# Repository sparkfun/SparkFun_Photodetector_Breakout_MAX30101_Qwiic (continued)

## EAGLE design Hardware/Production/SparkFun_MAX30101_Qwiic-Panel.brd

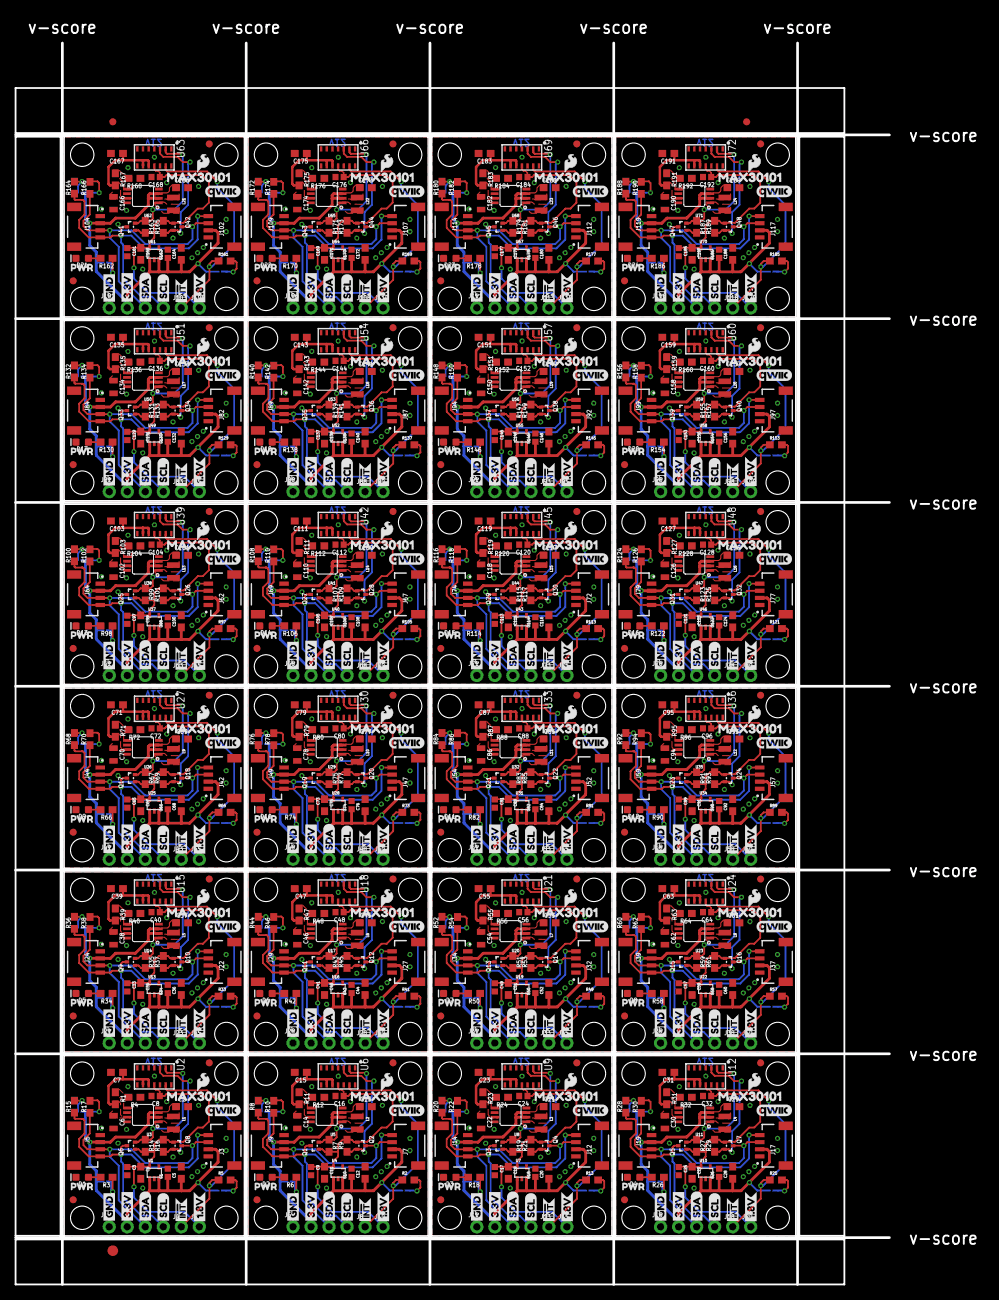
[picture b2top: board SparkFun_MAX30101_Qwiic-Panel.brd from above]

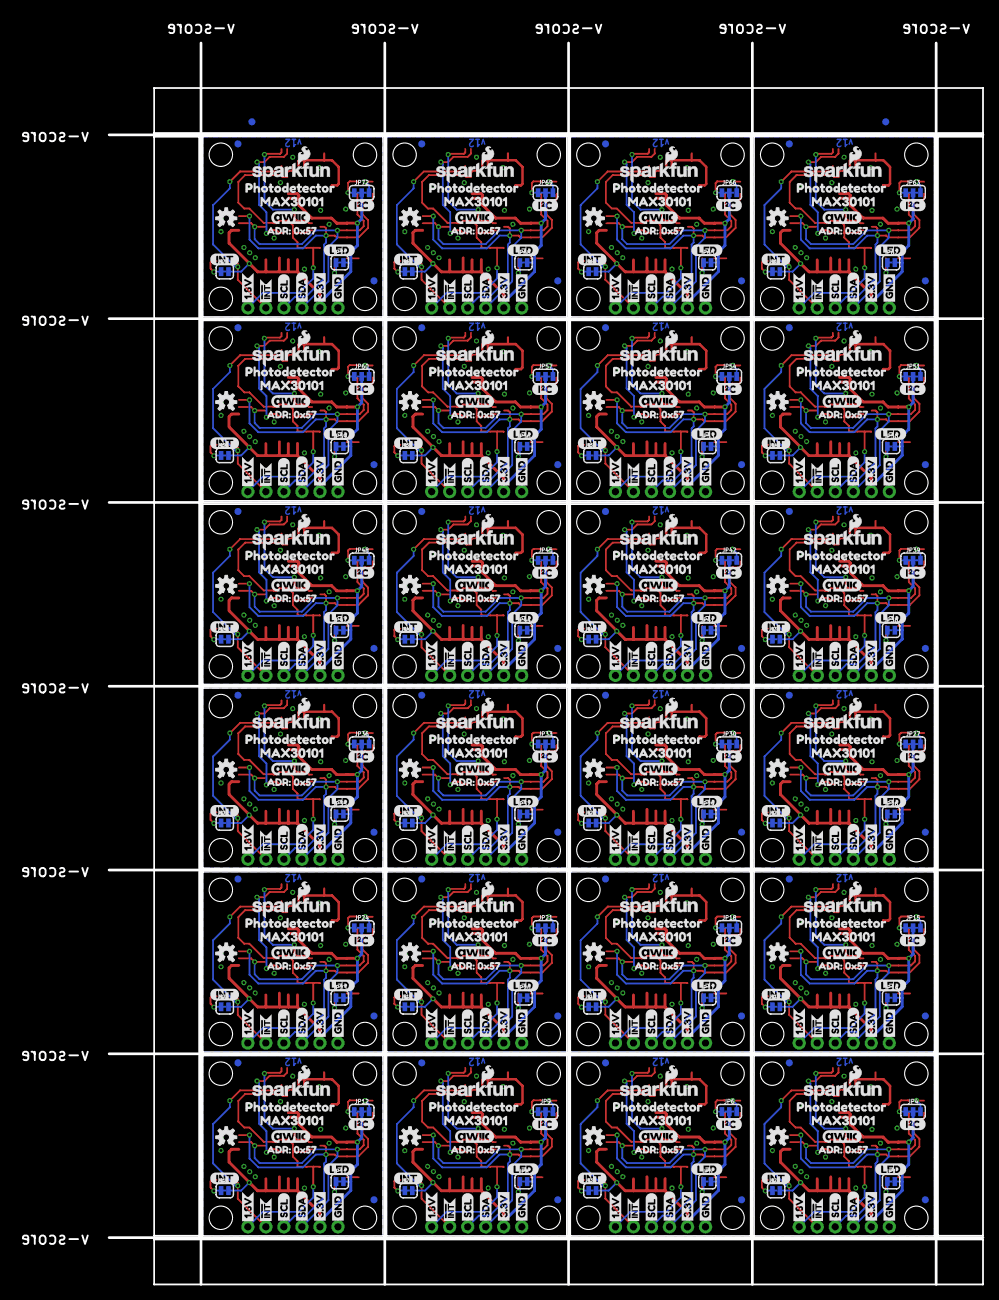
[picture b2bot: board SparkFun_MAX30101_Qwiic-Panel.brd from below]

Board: 2 copper layers, 123.2 x 175.0 mm, 1541 parts (482 on the bottom side), 384 nets.

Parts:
C1, C3, C8, C9, C10, C16, C17, C18, C24, C25, C26, C32, C33, C34, C40, C41, C42, C48, C49, C50, C56, C57, C58, C64, C65, C66, C72, C73, C74, C80, C81, C82, C88, C89, C90, C96, C97, C98, C104, C105, C106, C112, C113, C114, C120, C121, C122, C128, C129, C130, C136, C137, C138, C144, C145, C146, C152, C153, C154, C160, C161, C162, C168, C169, C170, C176, C177, C178, C184, C185, C186, C192: 0.1uF; 0402
C2, C4, C5, C7, C11, C12, C13, C15, C19, C20, C21, C23, C27, C28, C29, C31, C35, C36, C37, C39, C43, C44, C45, C47, C51, C52, C53, C55, C59, C60, C61, C63, C67, C68, C69, C71, C75, C76, C77, C79, C83, C84, C85, C87, C91, C92, C93, C95, C99, C100, C101, C103, C107, C108, C109, C111, C115, C116, C117, C119, C123, C124, C125, C127, C131, C132, C133, C135, C139, C140, C141, C143, C147, C148, C149, C151, C155, C156, C157, C159, C163, C164, C165, C167, C171, C172, C173, C175, C179, C180, C181, C183, C187, C188, C189, C191: 10uF; 0603
C6, C14, C22, C30, C38, C46, C54, C62, C70, C78, C86, C94, C102, C110, C118, C126, C134, C142, C150, C158, C166, C174, C182, C190: 22uF; 0805
D1, D2, D3, D4, D5, D6, D7, D8, D9, D10, D11, D12, D13, D14, D15, D16, D17, D18, D19, D20, D21, D22, D23, D24: RED; LED-0603
E$1, E$2, E$3, E$4: FIDUCIAL-1X2
E$5: FIDUCIAL-1.5X3
FID1, FID2, FID3, FID4, FID5, FID6, FID7, FID8, FID9, FID10, FID11, FID12, FID13, FID14, FID15, FID16, FID17, FID18, FID19, FID20, FID21, FID22, FID23, FID24, FID25, FID26, FID27, FID28, FID29, FID30, FID31, FID32, FID33, FID34, FID35, FID36, FID37, FID38, FID39, FID40, FID41, FID42, FID43, FID44, FID45, FID46, FID47, FID48, FID49, FID50, FID51, FID52, FID53, FID54, FID55, FID56, FID57, FID58, FID59, FID60, FID61, FID62, FID63, FID64, FID65, FID66, FID67, FID68, FID69, FID70, FID71, FID72, FID73, FID74, FID75, FID76, FID77, FID78, FID79, FID80, FID81, FID82, FID83, FID84, FID85, FID86, FID87, FID88, FID89, FID90, FID91, FID92, FID93, FID94, FID95, FID96: FIDUCIAL1X2; FIDUCIAL-1X2
J1, J6, J11, J16, J21, J26, J31, J36, J41, J46, J51, J56, J61, J66, J71, J76, J81, J86, J91, J96, J101, J106, J111, J116: PTH; 1X04_NO_SILK
J2, J4, J8, J10, J13, J15, J18, J20, J23, J25, J28, J30, J33, J35, J38, J40, J43, J45, J48, J50, J53, J55, J58, J60, J63, J65, J68, J70, J73, J75, J78, J80, J83, J85, J88, J90, J93, J95, J98, J100, J103, J105, J108, J110, J113, J115, J118, J120: 1X01_NO_SILK
J3, J5, J7, J9, J12, J14, J17, J19, J22, J24, J27, J29, J32, J34, J37, J39, J42, J44, J47, J49, J52, J54, J57, J59, J62, J64, J67, J69, J72, J74, J77, J79, J82, J84, J87, J89, J92, J94, J97, J99, J102, J104, J107, J109, J112, J114, J117, J119: QWIIC_RA; JST04_1MM_RA
JP1, JP5, JP8, JP11, JP14, JP17, JP20, JP23, JP26, JP29, JP32, JP35, JP38, JP41, JP44, JP47, JP50, JP53, JP56, JP59, JP62, JP65, JP68, JP71: LED; SMT-JUMPER_2_NC_TRACE_SILK
JP2, JP3, JP7, JP10, JP13, JP16, JP19, JP22, JP25, JP28, JP31, JP34, JP37, JP40, JP43, JP46, JP49, JP52, JP55, JP58, JP61, JP64, JP67, JP70: INT; SMT-JUMPER_2_NC_TRACE_SILK
JP4, JP6, JP9, JP12, JP15, JP18, JP21, JP24, JP27, JP30, JP33, JP36, JP39, JP42, JP45, JP48, JP51, JP54, JP57, JP60, JP63, JP66, JP69, JP72: I2C PU; SMT-JUMPER_3_2-NC_TRACE_SILK
L1, L2, L3, L4, L5, L6, L7, L8, L9, L10, L11, L12, L13, L14, L15, L16, L17, L18, L19, L20, L21, L22, L23, L24: 2.2μH; 0806
LOGO1, LOGO5, LOGO9, LOGO13, LOGO17, LOGO21, LOGO25, LOGO29, LOGO33, LOGO37, LOGO41, LOGO45, LOGO49, LOGO53, LOGO57, LOGO61, LOGO65, LOGO69, LOGO73, LOGO77, LOGO81, LOGO85, LOGO89, LOGO93: SFE_LOGO_NAME_FLAME.1_INCH; SFE_LOGO_NAME_FLAME_.1
LOGO2, LOGO6, LOGO10, LOGO14, LOGO18, LOGO22, LOGO26, LOGO30, LOGO34, LOGO38, LOGO42, LOGO46, LOGO50, LOGO54, LOGO58, LOGO62, LOGO66, LOGO70, LOGO74, LOGO78, LOGO82, LOGO86, LOGO90, LOGO94: OSHW-LOGOS; OSHW-LOGO-S
LOGO3, LOGO8, LOGO12, LOGO16, LOGO20, LOGO24, LOGO28, LOGO32, LOGO36, LOGO40, LOGO44, LOGO48, LOGO52, LOGO56, LOGO60, LOGO64, LOGO68, LOGO72, LOGO76, LOGO80, LOGO84, LOGO88, LOGO92, LOGO96: QWIIC_LOGO_5MM; QWIIC_5MM
LOGO4, LOGO7, LOGO11, LOGO15, LOGO19, LOGO23, LOGO27, LOGO31, LOGO35, LOGO39, LOGO43, LOGO47, LOGO51, LOGO55, LOGO59, LOGO63, LOGO67, LOGO71, LOGO75, LOGO79, LOGO83, LOGO87, LOGO91, LOGO95: SFE_LOGO_FLAME.1_INCH; SFE_LOGO_FLAME_.1
Q1, Q2, Q3, Q4, Q5, Q6, Q7, Q8, Q9, Q10, Q11, Q12, Q13, Q14, Q15, Q16, Q17, Q18, Q19, Q20, Q21, Q22, Q23, Q24, Q25, Q26, Q27, Q28, Q29, Q30, Q31, Q32, Q33, Q34, Q35, Q36, Q37, Q38, Q39, Q40, Q41, Q42, Q43, Q44, Q45, Q46, Q47, Q48: 20V/0.2A/8MHz/1.2Ω/1Vth; SOT-416FL
R1, R11, R23, R31, R39, R47, R55, R63, R71, R79, R87, R95, R103, R111, R119, R127, R135, R143, R151, R159, R167, R175, R183, R191: 750K; 0603
R2, R5, R13, R25, R33, R41, R49, R57, R65, R73, R81, R89, R97, R105, R113, R121, R129, R137, R145, R153, R161, R169, R177, R185: 4.7k; 0603
R3, R6, R18, R26, R34, R42, R50, R58, R66, R74, R82, R90, R98, R106, R114, R122, R130, R138, R146, R154, R162, R170, R178, R186: 1k; 0603
R4, R12, R24, R32, R40, R48, R56, R64, R72, R80, R88, R96, R104, R112, R120, R128, R136, R144, R152, R160, R168, R176, R184, R192: 100k; 0603
R7, R8, R9, R10, R14, R15, R16, R17, R19, R20, R21, R22, R27, R28, R29, R30, R35, R36, R37, R38, R43, R44, R45, R46, R51, R52, R53, R54, R59, R60, R61, R62, R67, R68, R69, R70, R75, R76, R77, R78, R83, R84, R85, R86, R91, R92, R93, R94, R99, R100, R101, R102, R107, R108, R109, R110, R115, R116, R117, R118, R123, R124, R125, R126, R131, R132, R133, R134, R139, R140, R141, R142, R147, R148, R149, R150, R155, R156, R157, R158, R163, R164, R165, R166, R171, R172, R173, R174, R179, R180, R181, R182, R187, R188, R189, R190: 2.2k; 0603
STANDOFF1, STANDOFF2, STANDOFF3, STANDOFF4, STANDOFF5, STANDOFF6, STANDOFF7, STANDOFF8, STANDOFF9, STANDOFF10, STANDOFF11, STANDOFF12, STANDOFF13, STANDOFF14, STANDOFF15, STANDOFF16, STANDOFF17, STANDOFF18, STANDOFF19, STANDOFF20, STANDOFF21, STANDOFF22, STANDOFF23, STANDOFF24, STANDOFF25, STANDOFF26, STANDOFF27, STANDOFF28, STANDOFF29, STANDOFF30, STANDOFF31, STANDOFF32, STANDOFF33, STANDOFF34, STANDOFF35, STANDOFF36, STANDOFF37, STANDOFF38, STANDOFF39, STANDOFF40, STANDOFF41, STANDOFF42, STANDOFF43, STANDOFF44, STANDOFF45, STANDOFF46, STANDOFF47, STANDOFF48, STANDOFF49, STANDOFF50, STANDOFF51, STANDOFF52, STANDOFF53, STANDOFF54, STANDOFF55, STANDOFF56, STANDOFF57, STANDOFF58, STANDOFF59, STANDOFF60, STANDOFF61, STANDOFF62, STANDOFF63, STANDOFF64, STANDOFF65, STANDOFF66, STANDOFF67, STANDOFF68, STANDOFF69, STANDOFF70, STANDOFF71, STANDOFF72, STANDOFF73, STANDOFF74, STANDOFF75, STANDOFF76, STANDOFF77, STANDOFF78, STANDOFF79, STANDOFF80, STANDOFF81, STANDOFF82, STANDOFF83, STANDOFF84, STANDOFF85, STANDOFF86, STANDOFF87, STANDOFF88, STANDOFF89, STANDOFF90, STANDOFF91, STANDOFF92, STANDOFF93, STANDOFF94, STANDOFF95, STANDOFF96: STAND-OFF
U1, U4, U7, U10, U13, U16, U19, U22, U25, U28, U31, U34, U37, U40, U43, U46, U49, U52, U55, U58, U61, U64, U67, U70: 1.8V/100mA; SC70
U2, U6, U9, U12, U15, U18, U21, U24, U27, U30, U33, U36, U39, U42, U45, U48, U51, U54, U57, U60, U63, U66, U69, U72: MAX30101EFD; 14_PIN_OESIP
U3, U5, U8, U11, U14, U17, U20, U23, U26, U29, U32, U35, U38, U41, U44, U47, U50, U53, U56, U59, U62, U65, U68, U71: PAM2401; MSOP8
U$1, U$42, U$63, U$84, U$105, U$126, U$147, U$168, U$189, U$210, U$231, U$252, U$273, U$294, U$315, U$336, U$357, U$378, U$399, U$420, U$441, U$462, U$483, U$504: PHOTODETECTOR3
U$2, U$3, U$6, U$11, U$43, U$45, U$64, U$66, U$85, U$87, U$106, U$108, U$127, U$129, U$148, U$150, U$169, U$171, U$190, U$192, U$211, U$213, U$232, U$234, U$253, U$255, U$274, U$276, U$295, U$297, U$316, U$318, U$337, U$339, U$358, U$360, U$379, U$381, U$400, U$402, U$421, U$423, U$442, U$444, U$463, U$465, U$484, U$486: INT#-[<-04
U$4, U$24, U$35, U$37, U$56, U$58, U$77, U$79, U$98, U$100, U$119, U$121, U$140, U$142, U$161, U$163, U$182, U$184, U$203, U$205, U$224, U$226, U$245, U$247, U$266, U$268, U$287, U$289, U$308, U$310, U$329, U$331, U$350, U$352, U$371, U$373, U$392, U$394, U$413, U$415, U$434, U$436, U$455, U$457, U$476, U$478, U$497, U$499: MAX301010
U$5, U$9, U$12, U$29, U$44, U$50, U$65, U$71, U$86, U$92, U$107, U$113, U$128, U$134, U$149, U$155, U$170, U$176, U$191, U$197, U$212, U$218, U$233, U$239, U$254, U$260, U$275, U$281, U$296, U$302, U$317, U$323, U$338, U$344, U$359, U$365, U$380, U$386, U$401, U$407, U$422, U$428, U$443, U$449, U$464, U$470, U$485, U$491: SCL-[)
U$7, U$32, U$53, U$74, U$95, U$116, U$137, U$158, U$179, U$200, U$221, U$242, U$263, U$284, U$305, U$326, U$347, U$368, U$389, U$410, U$431, U$452, U$473, U$494: INT-()-04
U$8, U$34, U$55, U$76, U$97, U$118, U$139, U$160, U$181, U$202, U$223, U$244, U$265, U$286, U$307, U$328, U$349, U$370, U$391, U$412, U$433, U$454, U$475, U$496: LED0
U$10, U$23, U$25, U$28, U$48, U$49, U$69, U$70, U$90, U$91, U$111, U$112, U$132, U$133, U$153, U$154, U$174, U$175, U$195, U$196, U$216, U$217, U$237, U$238, U$258, U$259, U$279, U$280, U$300, U$301, U$321, U$322, U$342, U$343, U$363, U$364, U$384, U$385, U$405, U$406, U$426, U$427, U$447, U$448, U$468, U$469, U$489, U$490: GND-04
U$13, U$14, U$30, U$31, U$51, U$52, U$72, U$73, U$93, U$94, U$114, U$115, U$135, U$136, U$156, U$157, U$177, U$178, U$198, U$199, U$219, U$220, U$240, U$241, U$261, U$262, U$282, U$283, U$303, U$304, U$324, U$325, U$345, U$346, U$366, U$367, U$387, U$388, U$408, U$409, U$429, U$430, U$450, U$451, U$471, U$472, U$492, U$493: SDA-[)
U$15, U$38, U$59, U$80, U$101, U$122, U$143, U$164, U$185, U$206, U$227, U$248, U$269, U$290, U$311, U$332, U$353, U$374, U$395, U$416, U$437, U$458, U$479, U$500: ADR#_0X570
U$16, U$36, U$57, U$78, U$99, U$120, U$141, U$162, U$183, U$204, U$225, U$246, U$267, U$288, U$309, U$330, U$351, U$372, U$393, U$414, U$435, U$456, U$477, U$498: QWIIC_5.5MM
U$17, U$18, U$19, U$22, U$46, U$47, U$67, U$68, U$88, U$89, U$109, U$110, U$130, U$131, U$151, U$152, U$172, U$173, U$193, U$194, U$214, U$215, U$235, U$236, U$256, U$257, U$277, U$278, U$298, U$299, U$319, U$320, U$340, U$341, U$361, U$362, U$382, U$383, U$403, U$404, U$424, U$425, U$445, U$446, U$466, U$467, U$487, U$488: 3.3V
U$20, U$27, U$40, U$41, U$61, U$62, U$82, U$83, U$103, U$104, U$124, U$125, U$145, U$146, U$166, U$167, U$187, U$188, U$208, U$209, U$229, U$230, U$250, U$251, U$271, U$272, U$292, U$293, U$313, U$314, U$334, U$335, U$355, U$356, U$376, U$377, U$397, U$398, U$418, U$419, U$439, U$440, U$460, U$461, U$481, U$482, U$502, U$503: 1#8V0
U$21, U$33, U$54, U$75, U$96, U$117, U$138, U$159, U$180, U$201, U$222, U$243, U$264, U$285, U$306, U$327, U$348, U$369, U$390, U$411, U$432, U$453, U$474, U$495: I_SUPER2_C-()-04
U$26, U$39, U$60, U$81, U$102, U$123, U$144, U$165, U$186, U$207, U$228, U$249, U$270, U$291, U$312, U$333, U$354, U$375, U$396, U$417, U$438, U$459, U$480, U$501: PWR_TO

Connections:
1.8V: C3.1, C4.1, C8.1, J2.1, Q6.1, Q8.1, R14.2, R16.2, U1.5, U2.P11
1.8V1: C9.1, C11.1, C16.1, J10.1, Q1.1, Q2.1, R7.2, R9.2, U4.5, U6.P11
1.8V2: C17.1, C19.1, C24.1, J15.1, Q3.1, Q4.1, R19.2, R21.2, U7.5, U9.P11
1.8V3: C25.1, C27.1, C32.1, J20.1, Q5.1, Q7.1, R27.2, R29.2, U10.5, U12.P11
1.8V4: C33.1, C35.1, C40.1, J25.1, Q9.1, Q10.1, R35.2, R37.2, U13.5, U15.P11
1.8V5: C41.1, C43.1, C48.1, J30.1, Q11.1, Q12.1, R43.2, R45.2, U16.5, U18.P11
1.8V6: C49.1, C51.1, C56.1, J35.1, Q13.1, Q14.1, R51.2, R53.2, U19.5, U21.P11
1.8V7: C57.1, C59.1, C64.1, J40.1, Q15.1, Q16.1, R59.2, R61.2, U22.5, U24.P11
1.8V8: C65.1, C67.1, C72.1, J45.1, Q17.1, Q18.1, R67.2, R69.2, U25.5, U27.P11
1.8V9: C73.1, C75.1, C80.1, J50.1, Q19.1, Q20.1, R75.2, R77.2, U28.5, U30.P11
1.8V10: C81.1, C83.1, C88.1, J55.1, Q21.1, Q22.1, R83.2, R85.2, U31.5, U33.P11
1.8V11: C89.1, C91.1, C96.1, J60.1, Q23.1, Q24.1, R91.2, R93.2, U34.5, U36.P11
1.8V12: C97.1, C99.1, C104.1, J65.1, Q25.1, Q26.1, R99.2, R101.2, U37.5, U39.P11
1.8V13: C105.1, C107.1, C112.1, J70.1, Q27.1, Q28.1, R107.2, R109.2, U40.5, U42.P11
1.8V14: C113.1, C115.1, C120.1, J75.1, Q29.1, Q30.1, R115.2, R117.2, U43.5, U45.P11
1.8V15: C121.1, C123.1, C128.1, J80.1, Q31.1, Q32.1, R123.2, R125.2, U46.5, U48.P11
1.8V16: C129.1, C131.1, C136.1, J85.1, Q33.1, Q34.1, R131.2, R133.2, U49.5, U51.P11
1.8V17: C137.1, C139.1, C144.1, J90.1, Q35.1, Q36.1, R139.2, R141.2, U52.5, U54.P11
1.8V18: C145.1, C147.1, C152.1, J95.1, Q37.1, Q38.1, R147.2, R149.2, U55.5, U57.P11
1.8V19: C153.1, C155.1, C160.1, J100.1, Q39.1, Q40.1, R155.2, R157.2, U58.5, U60.P11
1.8V20: C161.1, C163.1, C168.1, J105.1, Q41.1, Q42.1, R163.2, R165.2, U61.5, U63.P11
1.8V21: C169.1, C171.1, C176.1, J110.1, Q43.1, Q44.1, R171.2, R173.2, U64.5, U66.P11
1.8V22: C177.1, C179.1, C184.1, J115.1, Q45.1, Q46.1, R179.2, R181.2, U67.5, U69.P11
1.8V23: C185.1, C187.1, C192.1, J120.1, Q47.1, Q48.1, R187.2, R189.2, U70.5, U72.P11
3.3V: C1.1, C2.1, C5.1, J1.2, J3.2, J5.2, JP1.2, JP2.2, JP4.2, L1.1, U1.1, U1.3, U3.2, U3.3
3.3V1: C10.1, C12.1, C13.1, J6.2, J7.2, J9.2, JP3.2, JP5.2, JP6.2, L2.1, U4.1, U4.3, U5.2, U5.3
3.3V2: C18.1, C20.1, C21.1, J11.2, J12.2, J14.2, JP7.2, JP8.2, JP9.2, L3.1, U7.1, U7.3, U8.2, U8.3
3.3V3: C26.1, C28.1, C29.1, J16.2, J17.2, J19.2, JP10.2, JP11.2, JP12.2, L4.1, U10.1, U10.3, U11.2, U11.3
3.3V4: C34.1, C36.1, C37.1, J21.2, J22.2, J24.2, JP13.2, JP14.2, JP15.2, L5.1, U13.1, U13.3, U14.2, U14.3
3.3V5: C42.1, C44.1, C45.1, J26.2, J27.2, J29.2, JP16.2, JP17.2, JP18.2, L6.1, U16.1, U16.3, U17.2, U17.3
3.3V6: C50.1, C52.1, C53.1, J31.2, J32.2, J34.2, JP19.2, JP20.2, JP21.2, L7.1, U19.1, U19.3, U20.2, U20.3
3.3V7: C58.1, C60.1, C61.1, J36.2, J37.2, J39.2, JP22.2, JP23.2, JP24.2, L8.1, U22.1, U22.3, U23.2, U23.3
3.3V8: C66.1, C68.1, C69.1, J41.2, J42.2, J44.2, JP25.2, JP26.2, JP27.2, L9.1, U25.1, U25.3, U26.2, U26.3
3.3V9: C74.1, C76.1, C77.1, J46.2, J47.2, J49.2, JP28.2, JP29.2, JP30.2, L10.1, U28.1, U28.3, U29.2, U29.3
3.3V10: C82.1, C84.1, C85.1, J51.2, J52.2, J54.2, JP31.2, JP32.2, JP33.2, L11.1, U31.1, U31.3, U32.2, U32.3
3.3V11: C90.1, C92.1, C93.1, J56.2, J57.2, J59.2, JP34.2, JP35.2, JP36.2, L12.1, U34.1, U34.3, U35.2, U35.3
3.3V12: C98.1, C100.1, C101.1, J61.2, J62.2, J64.2, JP37.2, JP38.2, JP39.2, L13.1, U37.1, U37.3, U38.2, U38.3
3.3V13: C106.1, C108.1, C109.1, J66.2, J67.2, J69.2, JP40.2, JP41.2, JP42.2, L14.1, U40.1, U40.3, U41.2, U41.3
3.3V14: C114.1, C116.1, C117.1, J71.2, J72.2, J74.2, JP43.2, JP44.2, JP45.2, L15.1, U43.1, U43.3, U44.2, U44.3
3.3V15: C122.1, C124.1, C125.1, J76.2, J77.2, J79.2, JP46.2, JP47.2, JP48.2, L16.1, U46.1, U46.3, U47.2, U47.3
3.3V16: C130.1, C132.1, C133.1, J81.2, J82.2, J84.2, JP49.2, JP50.2, JP51.2, L17.1, U49.1, U49.3, U50.2, U50.3
3.3V17: C138.1, C140.1, C141.1, J86.2, J87.2, J89.2, JP52.2, JP53.2, JP54.2, L18.1, U52.1, U52.3, U53.2, U53.3
3.3V18: C146.1, C148.1, C149.1, J91.2, J92.2, J94.2, JP55.2, JP56.2, JP57.2, L19.1, U55.1, U55.3, U56.2, U56.3
3.3V19: C154.1, C156.1, C157.1, J96.2, J97.2, J99.2, JP58.2, JP59.2, JP60.2, L20.1, U58.1, U58.3, U59.2, U59.3
3.3V20: C162.1, C164.1, C165.1, J101.2, J102.2, J104.2, JP61.2, JP62.2, JP63.2, L21.1, U61.1, U61.3, U62.2, U62.3
3.3V21: C170.1, C172.1, C173.1, J106.2, J107.2, J109.2, JP64.2, JP65.2, JP66.2, L22.1, U64.1, U64.3, U65.2, U65.3
3.3V22: C178.1, C180.1, C181.1, J111.2, J112.2, J114.2, JP67.2, JP68.2, JP69.2, L23.1, U67.1, U67.3, U68.2, U68.3
3.3V23: C186.1, C188.1, C189.1, J116.2, J117.2, J119.2, JP70.2, JP71.2, JP72.2, L24.1, U70.1, U70.3, U71.2, U71.3
5V: C6.1, C7.1, R1.2, U2.P9, U2.P10, U3.7
5V1: C14.1, C15.1, R11.2, U5.7, U6.P9, U6.P10
5V2: C22.1, C23.1, R23.2, U8.7, U9.P9, U9.P10
5V3: C30.1, C31.1, R31.2, U11.7, U12.P9, U12.P10
5V4: C38.1, C39.1, R39.2, U14.7, U15.P9, U15.P10
5V5: C46.1, C47.1, R47.2, U17.7, U18.P9, U18.P10
5V6: C54.1, C55.1, R55.2, U20.7, U21.P9, U21.P10
5V7: C62.1, C63.1, R63.2, U23.7, U24.P9, U24.P10
5V8: C70.1, C71.1, R71.2, U26.7, U27.P9, U27.P10
5V9: C78.1, C79.1, R79.2, U29.7, U30.P9, U30.P10
5V10: C86.1, C87.1, R87.2, U32.7, U33.P9, U33.P10
5V11: C94.1, C95.1, R95.2, U35.7, U36.P9, U36.P10
5V12: C102.1, C103.1, R103.2, U38.7, U39.P9, U39.P10
5V13: C110.1, C111.1, R111.2, U41.7, U42.P9, U42.P10
5V14: C118.1, C119.1, R119.2, U44.7, U45.P9, U45.P10
5V15: C126.1, C127.1, R127.2, U47.7, U48.P9, U48.P10
5V16: C134.1, C135.1, R135.2, U50.7, U51.P9, U51.P10
5V17: C142.1, C143.1, R143.2, U53.7, U54.P9, U54.P10
5V18: C150.1, C151.1, R151.2, U56.7, U57.P9, U57.P10
5V19: C158.1, C159.1, R159.2, U59.7, U60.P9, U60.P10
5V20: C166.1, C167.1, R167.2, U62.7, U63.P9, U63.P10
5V21: C174.1, C175.1, R175.2, U65.7, U66.P9, U66.P10
5V22: C182.1, C183.1, R183.2, U68.7, U69.P9, U69.P10
5V23: C190.1, C191.1, R191.2, U71.7, U72.P9, U72.P10
!INT: J4.1, R5.1, U2.P13
!INT1: J8.1, R2.1, U6.P13
!INT2: J13.1, R13.1, U9.P13
!INT3: J18.1, R25.1, U12.P13
!INT4: J23.1, R33.1, U15.P13
!INT5: J28.1, R41.1, U18.P13
!INT6: J33.1, R49.1, U21.P13
!INT7: J38.1, R57.1, U24.P13
!INT8: J43.1, R65.1, U27.P13
!INT9: J48.1, R73.1, U30.P13
!INT10: J53.1, R81.1, U33.P13
!INT11: J58.1, R89.1, U36.P13
!INT12: J63.1, R97.1, U39.P13
!INT13: J68.1, R105.1, U42.P13
!INT14: J73.1, R113.1, U45.P13
!INT15: J78.1, R121.1, U48.P13
!INT16: J83.1, R129.1, U51.P13
!INT17: J88.1, R137.1, U54.P13
!INT18: J93.1, R145.1, U57.P13
!INT19: J98.1, R153.1, U60.P13
!INT20: J103.1, R161.1, U63.P13
!INT21: J108.1, R169.1, U66.P13
!INT22: J113.1, R177.1, U69.P13
!INT23: J118.1, R185.1, U72.P13
GND: C1.2, C2.2, C3.2, C4.2, C5.2, C6.2, C7.2, C8.2, D1.C, J1.1, J3.1, J5.1, R4.1, U1.2, U1.4, U2.P4, U2.P12, U3.4, U3.8
GND1: C9.2, C10.2, C11.2, C12.2, C13.2, C14.2, C15.2, C16.2, D2.C, J6.1, J7.1, J9.1, R12.1, U4.2, U4.4, U5.4, U5.8, U6.P4, U6.P12
GND2: C17.2, C18.2, C19.2, C20.2, C21.2, C22.2, C23.2, C24.2, D3.C, J11.1, J12.1, J14.1, R24.1, U7.2, U7.4, U8.4, U8.8, U9.P4, U9.P12
GND3: C25.2, C26.2, C27.2, C28.2, C29.2, C30.2, C31.2, C32.2, D4.C, J16.1, J17.1, J19.1, R32.1, U10.2, U10.4, U11.4, U11.8, U12.P4, U12.P12
GND4: C33.2, C34.2, C35.2, C36.2, C37.2, C38.2, C39.2, C40.2, D5.C, J21.1, J22.1, J24.1, R40.1, U13.2, U13.4, U14.4, U14.8, U15.P4, U15.P12
GND5: C41.2, C42.2, C43.2, C44.2, C45.2, C46.2, C47.2, C48.2, D6.C, J26.1, J27.1, J29.1, R48.1, U16.2, U16.4, U17.4, U17.8, U18.P4, U18.P12
GND6: C49.2, C50.2, C51.2, C52.2, C53.2, C54.2, C55.2, C56.2, D7.C, J31.1, J32.1, J34.1, R56.1, U19.2, U19.4, U20.4, U20.8, U21.P4, U21.P12
GND7: C57.2, C58.2, C59.2, C60.2, C61.2, C62.2, C63.2, C64.2, D8.C, J36.1, J37.1, J39.1, R64.1, U22.2, U22.4, U23.4, U23.8, U24.P4, U24.P12
GND8: C65.2, C66.2, C67.2, C68.2, C69.2, C70.2, C71.2, C72.2, D9.C, J41.1, J42.1, J44.1, R72.1, U25.2, U25.4, U26.4, U26.8, U27.P4, U27.P12
GND9: C73.2, C74.2, C75.2, C76.2, C77.2, C78.2, C79.2, C80.2, D10.C, J46.1, J47.1, J49.1, R80.1, U28.2, U28.4, U29.4, U29.8, U30.P4, U30.P12
GND10: C81.2, C82.2, C83.2, C84.2, C85.2, C86.2, C87.2, C88.2, D11.C, J51.1, J52.1, J54.1, R88.1, U31.2, U31.4, U32.4, U32.8, U33.P4, U33.P12
GND11: C89.2, C90.2, C91.2, C92.2, C93.2, C94.2, C95.2, C96.2, D12.C, J56.1, J57.1, J59.1, R96.1, U34.2, U34.4, U35.4, U35.8, U36.P4, U36.P12
GND12: C97.2, C98.2, C99.2, C100.2, C101.2, C102.2, C103.2, C104.2, D13.C, J61.1, J62.1, J64.1, R104.1, U37.2, U37.4, U38.4, U38.8, U39.P4, U39.P12
GND13: C105.2, C106.2, C107.2, C108.2, C109.2, C110.2, C111.2, C112.2, D14.C, J66.1, J67.1, J69.1, R112.1, U40.2, U40.4, U41.4, U41.8, U42.P4, U42.P12
GND14: C113.2, C114.2, C115.2, C116.2, C117.2, C118.2, C119.2, C120.2, D15.C, J71.1, J72.1, J74.1, R120.1, U43.2, U43.4, U44.4, U44.8, U45.P4, U45.P12
GND15: C121.2, C122.2, C123.2, C124.2, C125.2, C126.2, C127.2, C128.2, D16.C, J76.1, J77.1, J79.1, R128.1, U46.2, U46.4, U47.4, U47.8, U48.P4, U48.P12
GND16: C129.2, C130.2, C131.2, C132.2, C133.2, C134.2, C135.2, C136.2, D17.C, J81.1, J82.1, J84.1, R136.1, U49.2, U49.4, U50.4, U50.8, U51.P4, U51.P12
GND17: C137.2, C138.2, C139.2, C140.2, C141.2, C142.2, C143.2, C144.2, D18.C, J86.1, J87.1, J89.1, R144.1, U52.2, U52.4, U53.4, U53.8, U54.P4, U54.P12
GND18: C145.2, C146.2, C147.2, C148.2, C149.2, C150.2, C151.2, C152.2, D19.C, J91.1, J92.1, J94.1, R152.1, U55.2, U55.4, U56.4, U56.8, U57.P4, U57.P12
GND19: C153.2, C154.2, C155.2, C156.2, C157.2, C158.2, C159.2, C160.2, D20.C, J96.1, J97.1, J99.1, R160.1, U58.2, U58.4, U59.4, U59.8, U60.P4, U60.P12
GND20: C161.2, C162.2, C163.2, C164.2, C165.2, C166.2, C167.2, C168.2, D21.C, J101.1, J102.1, J104.1, R168.1, U61.2, U61.4, U62.4, U62.8, U63.P4, U63.P12
GND21: C169.2, C170.2, C171.2, C172.2, C173.2, C174.2, C175.2, C176.2, D22.C, J106.1, J107.1, J109.1, R176.1, U64.2, U64.4, U65.4, U65.8, U66.P4, U66.P12
GND22: C177.2, C178.2, C179.2, C180.2, C181.2, C182.2, C183.2, C184.2, D23.C, J111.1, J112.1, J114.1, R184.1, U67.2, U67.4, U68.4, U68.8, U69.P4, U69.P12
GND23: C185.2, C186.2, C187.2, C188.2, C189.2, C190.2, C191.2, C192.2, D24.C, J116.1, J117.1, J119.1, R192.1, U70.2, U70.4, U71.4, U71.8, U72.P4, U72.P12
LV_SCL: Q6.2, R14.1, U2.P2
LV_SCL1: Q1.2, R7.1, U6.P2
LV_SCL2: Q3.2, R19.1, U9.P2
LV_SCL3: Q5.2, R27.1, U12.P2
LV_SCL4: Q9.2, R35.1, U15.P2
LV_SCL5: Q11.2, R43.1, U18.P2
LV_SCL6: Q13.2, R51.1, U21.P2
LV_SCL7: Q15.2, R59.1, U24.P2
LV_SCL8: Q17.2, R67.1, U27.P2
LV_SCL9: Q19.2, R75.1, U30.P2
LV_SCL10: Q21.2, R83.1, U33.P2
LV_SCL11: Q23.2, R91.1, U36.P2
LV_SCL12: Q25.2, R99.1, U39.P2
LV_SCL13: Q27.2, R107.1, U42.P2
LV_SCL14: Q29.2, R115.1, U45.P2
LV_SCL15: Q31.2, R123.1, U48.P2
LV_SCL16: Q33.2, R131.1, U51.P2
LV_SCL17: Q35.2, R139.1, U54.P2
LV_SCL18: Q37.2, R147.1, U57.P2
LV_SCL19: Q39.2, R155.1, U60.P2
LV_SCL20: Q41.2, R163.1, U63.P2
LV_SCL21: Q43.2, R171.1, U66.P2
LV_SCL22: Q45.2, R179.1, U69.P2
LV_SCL23: Q47.2, R187.1, U72.P2
LV_SDA: Q8.2, R16.1, U2.P3
LV_SDA1: Q2.2, R9.1, U6.P3
LV_SDA2: Q4.2, R21.1, U9.P3
LV_SDA3: Q7.2, R29.1, U12.P3
LV_SDA4: Q10.2, R37.1, U15.P3
LV_SDA5: Q12.2, R45.1, U18.P3
LV_SDA6: Q14.2, R53.1, U21.P3
LV_SDA7: Q16.2, R61.1, U24.P3
LV_SDA8: Q18.2, R69.1, U27.P3
LV_SDA9: Q20.2, R77.1, U30.P3
LV_SDA10: Q22.2, R85.1, U33.P3
LV_SDA11: Q24.2, R93.1, U36.P3
LV_SDA12: Q26.2, R101.1, U39.P3
LV_SDA13: Q28.2, R109.1, U42.P3
LV_SDA14: Q30.2, R117.1, U45.P3
LV_SDA15: Q32.2, R125.1, U48.P3
LV_SDA16: Q34.2, R133.1, U51.P3
LV_SDA17: Q36.2, R141.1, U54.P3
LV_SDA18: Q38.2, R149.1, U57.P3
LV_SDA19: Q40.2, R157.1, U60.P3
LV_SDA20: Q42.2, R165.1, U63.P3
LV_SDA21: Q44.2, R173.1, U66.P3
LV_SDA22: Q46.2, R181.1, U69.P3
LV_SDA23: Q48.2, R189.1, U72.P3
unnamed: JP2.1, R5.2
unnamed: R1.1, R4.2, U3.5
unnamed: L1.2, U3.1
unnamed: D1.A, R3.2
unnamed: JP4.3, R15.2
unnamed: JP4.1, R17.2
unnamed: JP3.1, R2.2
unnamed: JP1.1, R3.1
unnamed: D2.A, R6.2
unnamed: JP5.1, R6.1
unnamed: JP6.3, R8.2
unnamed: JP6.1, R10.2
unnamed: R11.1, R12.2, U5.5
unnamed: L2.2, U5.1
unnamed: JP7.1, R13.2
unnamed: D3.A, R18.2
unnamed: JP8.1, R18.1
unnamed: JP9.3, R20.2
unnamed: JP9.1, R22.2
unnamed: R23.1, R24.2, U8.5
unnamed: L3.2, U8.1
unnamed: JP10.1, R25.2
unnamed: D4.A, R26.2
unnamed: JP11.1, R26.1
unnamed: JP12.3, R28.2
unnamed: JP12.1, R30.2
unnamed: R31.1, R32.2, U11.5
unnamed: L4.2, U11.1
unnamed: JP13.1, R33.2
unnamed: D5.A, R34.2
unnamed: JP14.1, R34.1
unnamed: JP15.3, R36.2
unnamed: JP15.1, R38.2
unnamed: R39.1, R40.2, U14.5
unnamed: L5.2, U14.1
unnamed: JP16.1, R41.2
unnamed: D6.A, R42.2
unnamed: JP17.1, R42.1
unnamed: JP18.3, R44.2
unnamed: JP18.1, R46.2
unnamed: R47.1, R48.2, U17.5
unnamed: L6.2, U17.1
unnamed: JP19.1, R49.2
unnamed: D7.A, R50.2
unnamed: JP20.1, R50.1
unnamed: JP21.3, R52.2
unnamed: JP21.1, R54.2
unnamed: R55.1, R56.2, U20.5
unnamed: L7.2, U20.1
unnamed: JP22.1, R57.2
unnamed: D8.A, R58.2
unnamed: JP23.1, R58.1
unnamed: JP24.3, R60.2
unnamed: JP24.1, R62.2
unnamed: R63.1, R64.2, U23.5
unnamed: L8.2, U23.1
unnamed: JP25.1, R65.2
unnamed: D9.A, R66.2
unnamed: JP26.1, R66.1
unnamed: JP27.3, R68.2
unnamed: JP27.1, R70.2
unnamed: R71.1, R72.2, U26.5
unnamed: L9.2, U26.1
unnamed: JP28.1, R73.2
unnamed: D10.A, R74.2
unnamed: JP29.1, R74.1
unnamed: JP30.3, R76.2
unnamed: JP30.1, R78.2
unnamed: R79.1, R80.2, U29.5
unnamed: L10.2, U29.1
unnamed: JP31.1, R81.2
unnamed: D11.A, R82.2
unnamed: JP32.1, R82.1
unnamed: JP33.3, R84.2
unnamed: JP33.1, R86.2
unnamed: R87.1, R88.2, U32.5
unnamed: L11.2, U32.1
unnamed: JP34.1, R89.2
unnamed: D12.A, R90.2
unnamed: JP35.1, R90.1
unnamed: JP36.3, R92.2
unnamed: JP36.1, R94.2
unnamed: R95.1, R96.2, U35.5
unnamed: L12.2, U35.1
unnamed: JP37.1, R97.2
unnamed: D13.A, R98.2
unnamed: JP38.1, R98.1
unnamed: JP39.3, R100.2
unnamed: JP39.1, R102.2
unnamed: R103.1, R104.2, U38.5
unnamed: L13.2, U38.1
unnamed: JP40.1, R105.2
unnamed: D14.A, R106.2
unnamed: JP41.1, R106.1
unnamed: JP42.3, R108.2
unnamed: JP42.1, R110.2
unnamed: R111.1, R112.2, U41.5
unnamed: L14.2, U41.1
unnamed: JP43.1, R113.2
unnamed: D15.A, R114.2
unnamed: JP44.1, R114.1
unnamed: JP45.3, R116.2
unnamed: JP45.1, R118.2
unnamed: R119.1, R120.2, U44.5
unnamed: L15.2, U44.1
unnamed: JP46.1, R121.2
unnamed: D16.A, R122.2
unnamed: JP47.1, R122.1
unnamed: JP48.3, R124.2
unnamed: JP48.1, R126.2
unnamed: R127.1, R128.2, U47.5
unnamed: L16.2, U47.1
unnamed: JP49.1, R129.2
unnamed: D17.A, R130.2
unnamed: JP50.1, R130.1
unnamed: JP51.3, R132.2
unnamed: JP51.1, R134.2
unnamed: R135.1, R136.2, U50.5
unnamed: L17.2, U50.1
unnamed: JP52.1, R137.2
unnamed: D18.A, R138.2
unnamed: JP53.1, R138.1
unnamed: JP54.3, R140.2
unnamed: JP54.1, R142.2
unnamed: R143.1, R144.2, U53.5
unnamed: L18.2, U53.1
unnamed: JP55.1, R145.2
unnamed: D19.A, R146.2
unnamed: JP56.1, R146.1
unnamed: JP57.3, R148.2
unnamed: JP57.1, R150.2
unnamed: R151.1, R152.2, U56.5
unnamed: L19.2, U56.1
unnamed: JP58.1, R153.2
unnamed: D20.A, R154.2
unnamed: JP59.1, R154.1
unnamed: JP60.3, R156.2
unnamed: JP60.1, R158.2
unnamed: R159.1, R160.2, U59.5
unnamed: L20.2, U59.1
unnamed: JP61.1, R161.2
unnamed: D21.A, R162.2
unnamed: JP62.1, R162.1
unnamed: JP63.3, R164.2
unnamed: JP63.1, R166.2
unnamed: R167.1, R168.2, U62.5
unnamed: L21.2, U62.1
unnamed: JP64.1, R169.2
unnamed: D22.A, R170.2
unnamed: JP65.1, R170.1
unnamed: JP66.3, R172.2
unnamed: JP66.1, R174.2
unnamed: R175.1, R176.2, U65.5
unnamed: L22.2, U65.1
unnamed: JP67.1, R177.2
unnamed: D23.A, R178.2
unnamed: JP68.1, R178.1
unnamed: JP69.3, R180.2
unnamed: JP69.1, R182.2
unnamed: R183.1, R184.2, U68.5
unnamed: L23.2, U68.1
unnamed: JP70.1, R185.2
unnamed: D24.A, R186.2
unnamed: JP71.1, R186.1
unnamed: JP72.3, R188.2
unnamed: JP72.1, R190.2
unnamed: R191.1, R192.2, U71.5
unnamed: L24.2, U71.1
SCL: J1.4, J3.4, J5.4, Q6.3, R15.1
SCL1: J6.4, J7.4, J9.4, Q1.3, R8.1
SCL2: J11.4, J12.4, J14.4, Q3.3, R20.1
SCL3: J16.4, J17.4, J19.4, Q5.3, R28.1
SCL4: J21.4, J22.4, J24.4, Q9.3, R36.1
SCL5: J26.4, J27.4, J29.4, Q11.3, R44.1
SCL6: J31.4, J32.4, J34.4, Q13.3, R52.1
SCL7: J36.4, J37.4, J39.4, Q15.3, R60.1
SCL8: J41.4, J42.4, J44.4, Q17.3, R68.1
SCL9: J46.4, J47.4, J49.4, Q19.3, R76.1
SCL10: J51.4, J52.4, J54.4, Q21.3, R84.1
SCL11: J56.4, J57.4, J59.4, Q23.3, R92.1
SCL12: J61.4, J62.4, J64.4, Q25.3, R100.1
SCL13: J66.4, J67.4, J69.4, Q27.3, R108.1
SCL14: J71.4, J72.4, J74.4, Q29.3, R116.1
SCL15: J76.4, J77.4, J79.4, Q31.3, R124.1
SCL16: J81.4, J82.4, J84.4, Q33.3, R132.1
SCL17: J86.4, J87.4, J89.4, Q35.3, R140.1
SCL18: J91.4, J92.4, J94.4, Q37.3, R148.1
SCL19: J96.4, J97.4, J99.4, Q39.3, R156.1
SCL20: J101.4, J102.4, J104.4, Q41.3, R164.1
SCL21: J106.4, J107.4, J109.4, Q43.3, R172.1
SCL22: J111.4, J112.4, J114.4, Q45.3, R180.1
SCL23: J116.4, J117.4, J119.4, Q47.3, R188.1
SDA: J1.3, J3.3, J5.3, Q8.3, R17.1
SDA1: J6.3, J7.3, J9.3, Q2.3, R10.1
SDA2: J11.3, J12.3, J14.3, Q4.3, R22.1
SDA3: J16.3, J17.3, J19.3, Q7.3, R30.1
SDA4: J21.3, J22.3, J24.3, Q10.3, R38.1
SDA5: J26.3, J27.3, J29.3, Q12.3, R46.1
SDA6: J31.3, J32.3, J34.3, Q14.3, R54.1
SDA7: J36.3, J37.3, J39.3, Q16.3, R62.1
SDA8: J41.3, J42.3, J44.3, Q18.3, R70.1
SDA9: J46.3, J47.3, J49.3, Q20.3, R78.1
SDA10: J51.3, J52.3, J54.3, Q22.3, R86.1
SDA11: J56.3, J57.3, J59.3, Q24.3, R94.1
SDA12: J61.3, J62.3, J64.3, Q26.3, R102.1
SDA13: J66.3, J67.3, J69.3, Q28.3, R110.1
SDA14: J71.3, J72.3, J74.3, Q30.3, R118.1
SDA15: J76.3, J77.3, J79.3, Q32.3, R126.1
SDA16: J81.3, J82.3, J84.3, Q34.3, R134.1
SDA17: J86.3, J87.3, J89.3, Q36.3, R142.1
SDA18: J91.3, J92.3, J94.3, Q38.3, R150.1
SDA19: J96.3, J97.3, J99.3, Q40.3, R158.1
SDA20: J101.3, J102.3, J104.3, Q42.3, R166.1
SDA21: J106.3, J107.3, J109.3, Q44.3, R174.1
SDA22: J111.3, J112.3, J114.3, Q46.3, R182.1
SDA23: J116.3, J117.3, J119.3, Q48.3, R190.1

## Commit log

2020-03-26 v10 hardware design files
2020-03-27 Qwiic logo in SCH and sch cleanup
2020-03-27 Added I2C address to bottom silk
2020-04-10 Added 5V step up for green LED and review changes
    -Added in 5V step up circuit to provide 5V for Green LED
    -Add fids to bottom
    -move power led label to text only
    -3.3V trace could loose a via and then stitch up gnd with more vias
    -move IC device to the true MAX30105 in the library.
    -flip v10 in copper to read "along" the bottom.
2020-04-10 design review #2 changes (post DC-DC converter addition)
    -cleaned up sch around DC-DC converter
    -added silk outline to MAX30101 IC
    -replaced 4.7K resistor to updated package (without silk under it)
    -updated Mosfets on logic level translation to latest library devices
2020-04-16 Added more bypass caps to 5V and 1.8V, bumped version to v11
2020-04-16 Production panel file and gerbers
2020-05-27 datasheet
2020-05-27 Updated name silk to "Photodetector"
    Also bumped version to v12 on sch and brd
2020-05-27 Production panel updated to v12
2020-06-03 adding license and more
2020-06-25 Update README.md
    Fix image link
2020-06-25 Update README.md
    Fix image link (try #2)
